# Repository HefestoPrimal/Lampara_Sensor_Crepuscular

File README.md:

# Lámpara con sensor crepuscular

A través de una fotocelda que detecta los niveles de luz se controla un relevador con una carga para encender o apagar una lámpara según el nivel detectado con un control de sensibilidad para personalizar el punto en el que la lampara se encienda.

**PCB Terminada**

**Vista en 3D de la placa**

## Características

- Automatización sin necesidad de programación
- Diseño de PCB especial para el proyecto
- Control de setpoint directo en el proyecto

## Estructura del repositorio
**Docs:** Contiene fotos y videos más detallados del funcionamiento del proyecto
**Hardware:** Contiene los archivos necesarios para replicar el proyecto, esquemáticos, archivos gerber, BOM (Bill of materialls) y POS (Archivos de posición para el pedido de la PCB)

## Cómo empezar

En caso de no tener la PCB del proyecto siga las conexiones indicadas del esquemático en una protoboard teniendo precaución extra en la parte de potencia de la lampara para evitar accidentes, se recomienda hacer una prueba con un elemento simple que muestre su funcionamiento, por ejemplo un LED.

En caso de tener la PCB del proyecto, solo hace falta soldar según la asignación del componente que se indica en la misma placa por el reverso.

## Enlaces
- [Portafolio](https://github.com/HefestoPrimal/Portafolio)
- [Linkedin](https://www.linkedin.com/in/angel-diaz-mexatronica/)
- [YouTube](https://youtube.com/@mexatronica99)
- [Facebook](https://www.facebook.com/mexatronica99)
- [Instagram](https://www.instagram.com/mexatronica99/)
- [Pinterest](https://mx.pinterest.com/mexatronica99/)
- [TikTok](https://www.tiktok.com/@mexatronica99)

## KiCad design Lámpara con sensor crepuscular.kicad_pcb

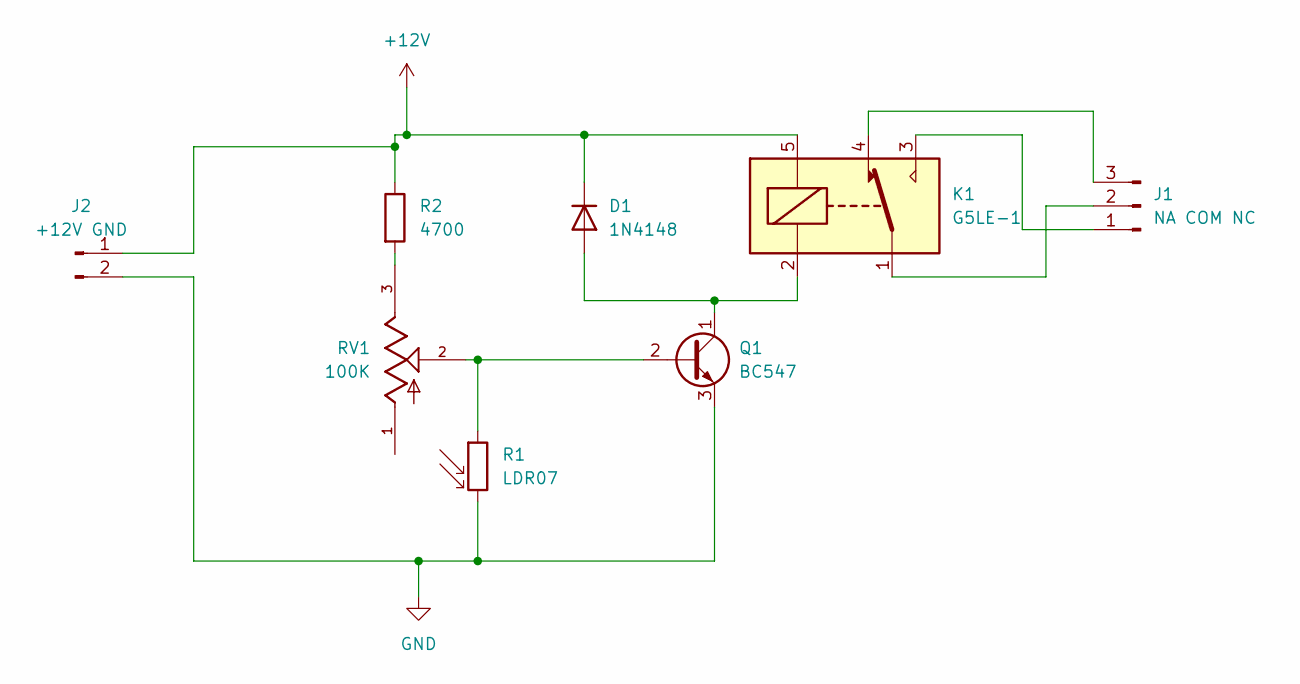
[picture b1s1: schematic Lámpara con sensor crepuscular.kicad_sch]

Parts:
D1: 1N4148; D_DO-35_SOD27_P7.62mm_Horizontal
J1: NA COM NC; TerminalBlock_MaiXu_MX126-5.0-03P_1x03_P5.00mm
J2: +12V GND; Altech_AK100_1x02_P5.00mm
K1: G5LE-1; Relay_SPDT_Omron-G5LE-1
Q1: BC547; TO-92_Inline
R1: LDR07; R_LDR_5.1x4.3mm_P3.4mm_Vertical
R2: 4700; R_Axial_DIN0204_L3.6mm_D1.6mm_P7.62mm_Horizontal
RV1: 100K; TRIM_3362P-1-503RLF; PARTREV 08/26/10

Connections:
+12V: D1.1 (K), J2.1, K1.5, R2.1
GND: J2.2, Q1.3 (E), R1.2
unnamed: D1.2 (A), K1.2, Q1.1 (C)
unnamed: J1.1, K1.3
unnamed: J1.2, K1.1
unnamed: J1.3, K1.4
unnamed: Q1.2 (B), R1.1, RV1.2
unnamed: R2.2, RV1.3

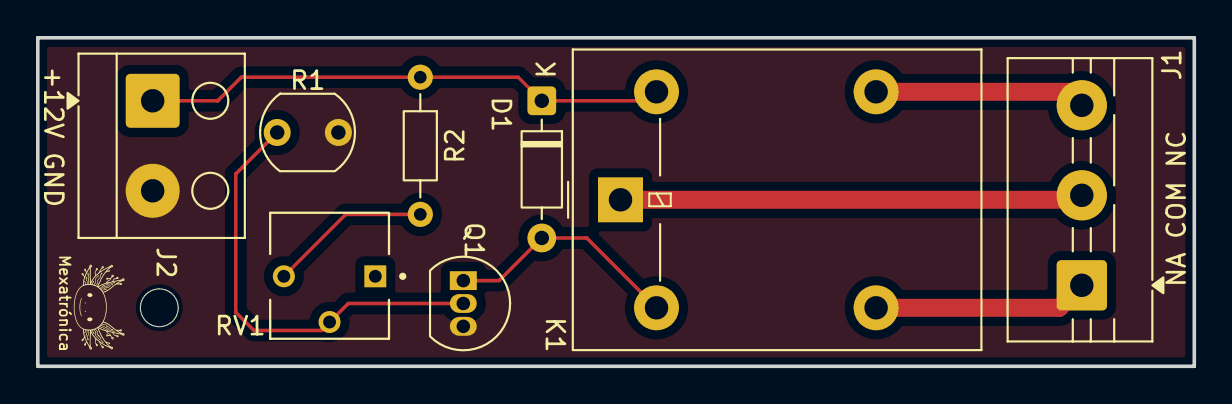
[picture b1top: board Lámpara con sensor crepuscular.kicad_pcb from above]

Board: 2 copper layers, 64.2 x 18.2 mm, 8 parts (0 on the bottom side), 8 nets.

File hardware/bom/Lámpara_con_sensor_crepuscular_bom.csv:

Designator,Footprint,Quantity,Value,LCSC Part #
D1,D_DO-35_SOD27_P7.62mm_Horizontal,1,1N4148,
J1,TerminalBlock_MaiXu_MX126-5.0-03P_1x03_P5.00mm,1,NA COM NC,
J2,Altech_AK100_1x02_P5.00mm,1,+12V GND,
K1,Relay_SPDT_Omron-G5LE-1,1,G5LE-1,
Q1,TO-92_Inline,1,BC547,
R1,R_LDR_5.1x4.3mm_P3.4mm_Vertical,1,LDR07,
R2,R_Axial_DIN0204_L3.6mm_D1.6mm_P7.62mm_Horizontal,1,4700,
RV1,TRIM_3362P-1-503RLF,1,100K,

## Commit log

2026-03-27 Primera versión funcional lista para produccion, DRC correctos
2026-03-27 Añadir carpetas para guardar los archivos gerber, POS y BOM organizados por carpetas, hacer un README correspondiente al proyecto, colocar imagenes y videos referentes al proyecto como visualización 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
2026-03-27 Correcciones en README para mostrar imágenes del proyecto y quitar archivo innecesario del repositorio
2026-03-27 Corrección de rutas en imagenes para mostrarse en el README
2026-03-27 Prueba y corrección de visualización de imagenes en el README
2026-03-27 Corrección completa de imagenes en el README para que aparezcan con titulo y tamaño adecuado
2026-03-27 Ajustar ancho de visualizador en 3D de la placa
